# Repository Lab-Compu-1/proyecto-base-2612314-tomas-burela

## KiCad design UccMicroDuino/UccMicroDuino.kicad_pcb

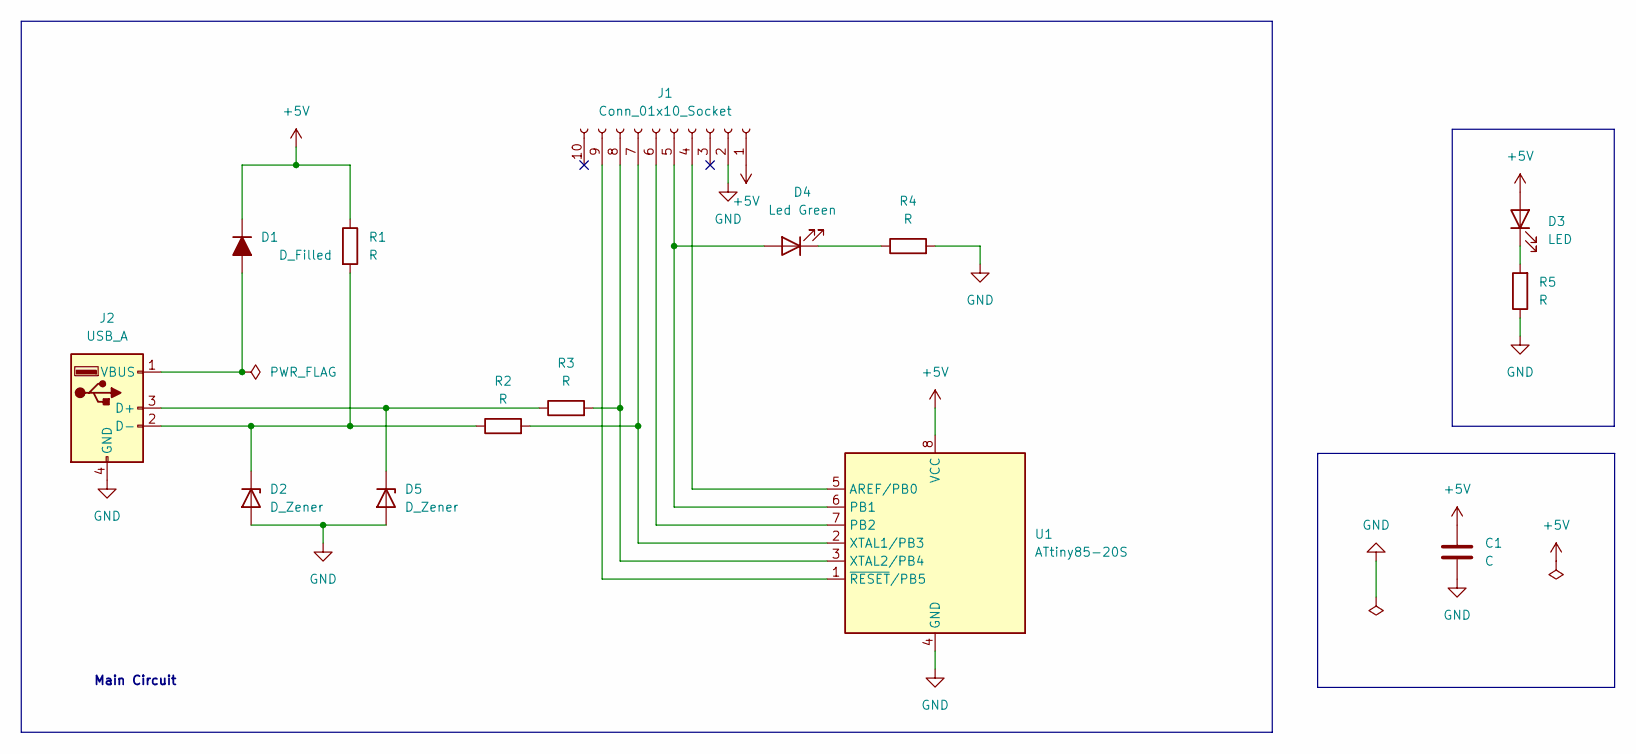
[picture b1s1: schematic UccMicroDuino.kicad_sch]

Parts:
C1: C; C_0805_2012Metric_Pad1.18x1.45mm_HandSolder
D1: D_Filled; D_MiniMELF
D2, D5: D_Zener; D_SOD-123
D3: LED; ledSMD
D4: Led Green; ledSMD
J1: Conn_01x10_Socket; PinHeader_1x10_P2.54mm_Vertical
J2: USB_A; USB_A_UCC
R1, R2, R3, R4, R5: R; R_0805_2012Metric_Pad1.20x1.40mm_HandSolder
U1: ATtiny85-20S; SOIC-8_5.3x5.3mm_P1.27mm

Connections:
+5V: C1.1, D1.1 (K), D3.2 (A), J1.1, R1.1, U1.8 (VCC)
GND: C1.2, D2.2 (A), D5.2 (A), J1.2, J2.4 (GND), R4.2, R5.1, U1.4 (GND)
unnamed: D1.2 (A), J2.1 (VBUS)
unnamed: D2.1 (K), J2.2 (D-), R1.2, R2.1
unnamed: D3.1 (K), R5.2
unnamed: D4.2 (A), J1.5, U1.6 (PB1)
unnamed: D4.1 (K), R4.1
unnamed: D5.1 (K), J2.3 (D+), R3.1
unnamed: J1.4, U1.5 (AREF/PB0)
unnamed: J1.6, U1.7 (PB2)
unnamed: J1.7, R2.2, U1.2 (XTAL1/PB3)
unnamed: J1.8, R3.2, U1.3 (XTAL2/PB4)
unnamed: J1.9, U1.1 (~RESET/PB5)

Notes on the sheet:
Main Circuit

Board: 2 copper layers, 14 parts (0 on the bottom side), 13 nets, no tracks yet.

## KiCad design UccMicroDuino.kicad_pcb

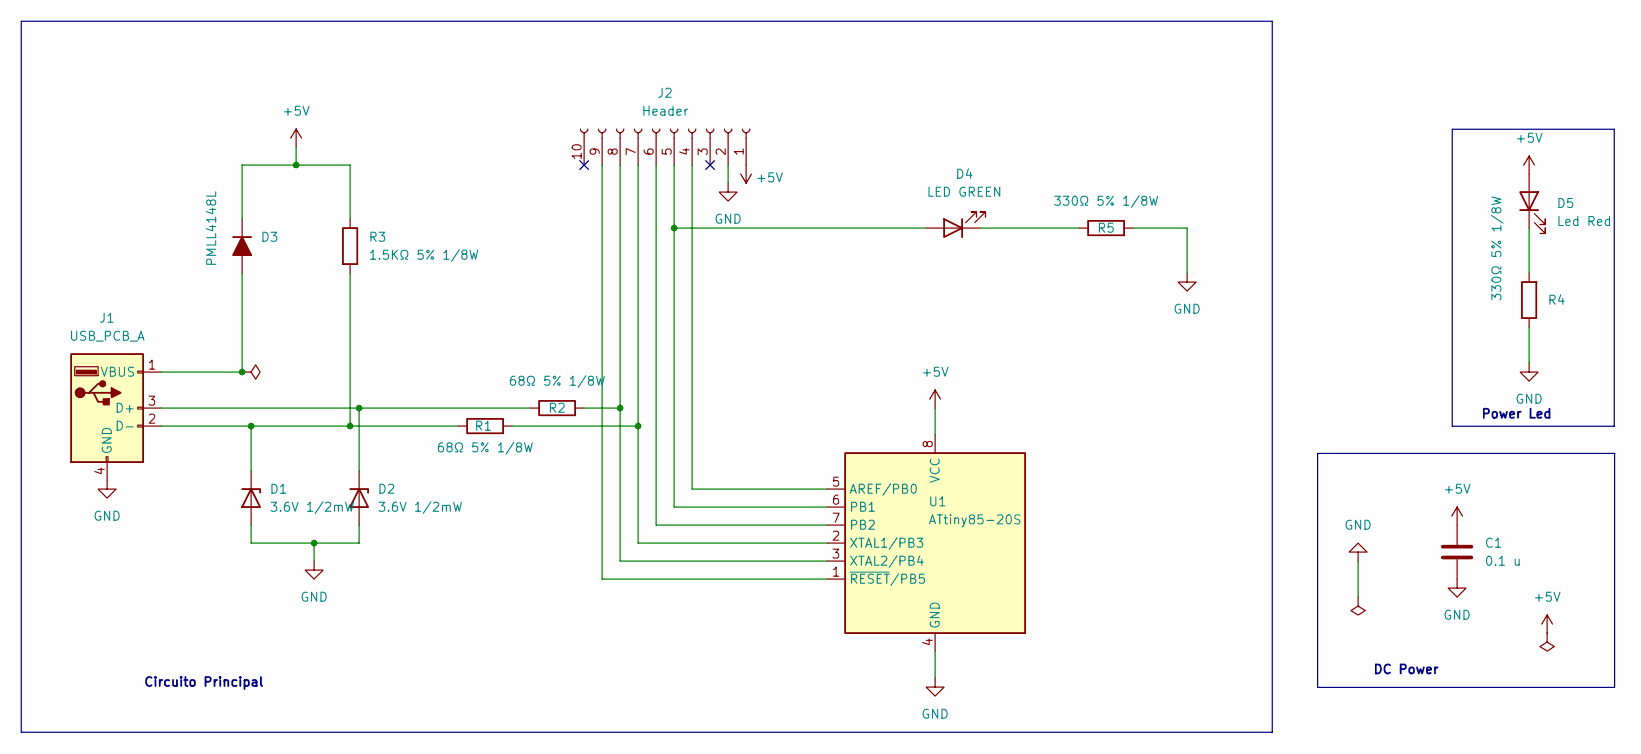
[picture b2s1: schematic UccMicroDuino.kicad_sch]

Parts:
C1: 0.1 u; C_0805_2012Metric_Pad1.18x1.45mm_HandSolder
D1, D2: 3.6V 1/2mW; D_SOD-123
D3: PMLL4148L; D_MiniMELF
D4: LED GREEN; ledSMD
D5: Led Red; ledSMD
J1: USB_PCB_A; USB_A_UCC
J2: Header; PinHeader_1x10_P2.54mm_Vertical
R1, R2: 68Ω 5% 1/8W; R_0805_2012Metric_Pad1.20x1.40mm_HandSolder
R3: 1.5KΩ 5% 1/8W; R_0805_2012Metric_Pad1.20x1.40mm_HandSolder
R4, R5: 330Ω 5% 1/8W; R_0805_2012Metric_Pad1.20x1.40mm_HandSolder
U1: ATtiny85-20S; SOIC-8_5.3x5.3mm_P1.27mm

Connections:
+5V: C1.1, D3.1 (K), D5.2 (A), J2.1, R3.1, U1.8 (VCC)
GND: C1.2, D1.2 (A), D2.2 (A), J1.4 (GND), J2.2, R4.1, R5.2, U1.4 (GND)
unnamed: D1.1 (K), J1.2 (D-), R1.1, R3.2
unnamed: D2.1 (K), J1.3 (D+), R2.1
unnamed: D3.2 (A), J1.1 (VBUS)
unnamed: D4.2 (A), J2.5, U1.6 (PB1)
unnamed: D4.1 (K), R5.1
unnamed: D5.1 (K), R4.2
unnamed: J2.4, U1.5 (AREF/PB0)
unnamed: J2.6, U1.7 (PB2)
unnamed: J2.7, R1.2, U1.2 (XTAL1/PB3)
unnamed: J2.8, R2.2, U1.3 (XTAL2/PB4)
unnamed: J2.9, U1.1 (~RESET/PB5)

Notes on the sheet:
Power Led
Circuito Principal
DC Power

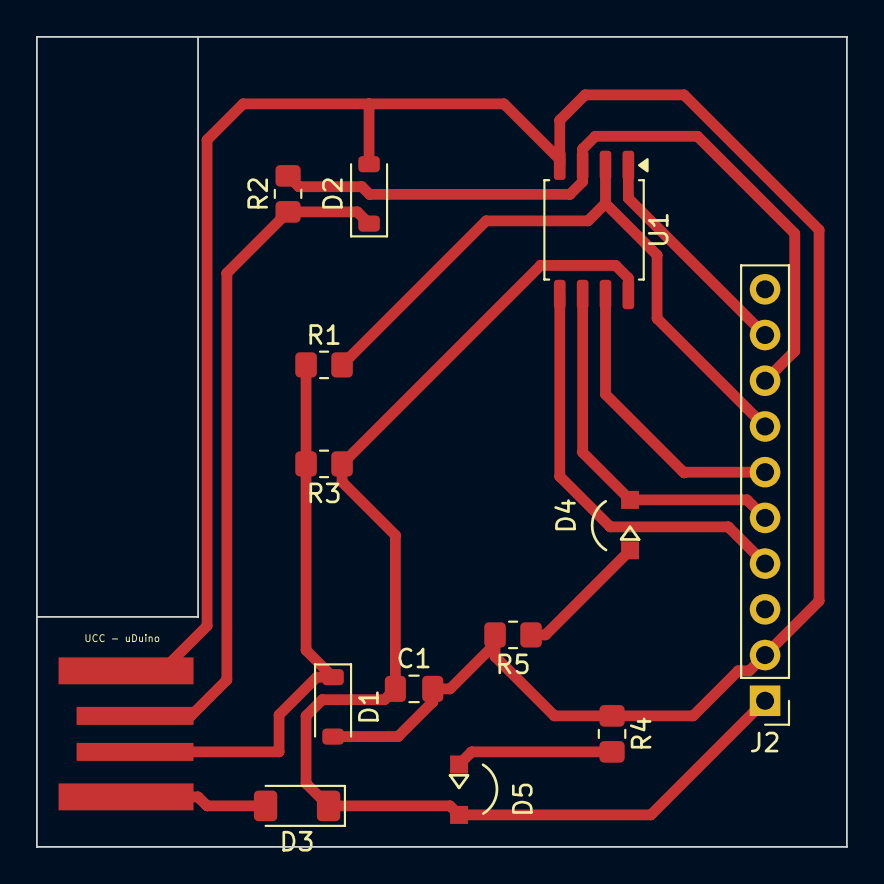
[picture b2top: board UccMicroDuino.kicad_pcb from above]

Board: 2 copper layers, 45.0 x 45.0 mm, 14 parts (0 on the bottom side), 13 nets.

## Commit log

2026-03-30 GitHub Classroom Feedback
2026-03-30 Setting up GitHub Classroom Feedback
2026-06-01 mi primer versionado de git
